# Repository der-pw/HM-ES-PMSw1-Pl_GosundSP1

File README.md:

# HM-ES-PMSw1-Pl_GosundSP1 PCB Version 2         

Umbau [Gosund SP1 bzw. BliTZWOLF SHP2](https://www.blitzwolf.com/Wifi-Smart-Socket-EU-p-244.html) zu HM-ES-PMSw1-Pl_SP1

In dieser Version 2 habe ich das Platinenlayout von [stan23](https://github.com/stan23) geändert.
Die SMD-Bauteile wurden auf Größe 0805 geändert und nur auf einer Seite arangiert, sodass einzig das Radio auf der Rückseite verbleibt und somit der Pinheader nicht mehr benötigt wird.

Weiterhin liegt das Original-Projekt hier: https://github.com/stan23/HM-ES-PMSw1-Pl_GosundSP1

Dies basiert auf der hervorragenden Arbeit von [pa-pa](https://github.com/pa-pa/AskSinPP) und [Jérôme](https://github.com/jp112sdl/Beispiel_AskSinPP).

*Achtung*: es kann verschiedene Versionen der Gosund/Blitzwolf-Stecker geben. Diese Platine passt bei folgender Version:

## Teileliste
Bauteil                  | Bestellnummer   | Anzahl | Kommentar
------------------------ | --------------- | ------ | ---------
C1                       | X5R-G0805 10/6  |   1    | -
C2 .. C6                 | X7R-G0805 100N  |   5    | -
R1                       | RND 0805 1 10K  |   1    | -
R2                       | RND 0805 1 1,0M |   1    | -
U1                       | ATMEGA 644PA-AU |   1    | -
Y1                       | CSTCE 8,00      |   1    | ist EOL, aber über Ali noch zu beziehen

## Vergleich:

## Eingebaut

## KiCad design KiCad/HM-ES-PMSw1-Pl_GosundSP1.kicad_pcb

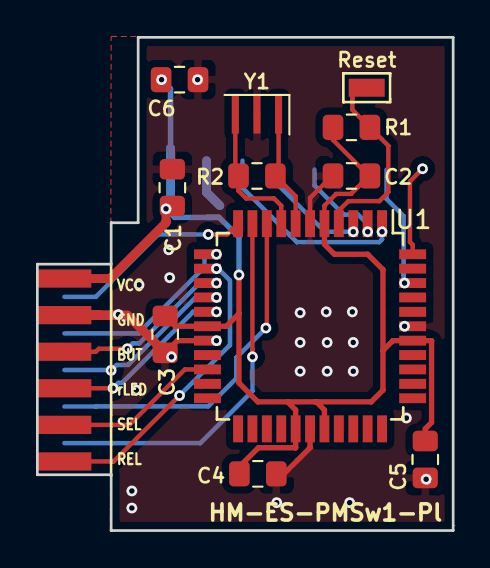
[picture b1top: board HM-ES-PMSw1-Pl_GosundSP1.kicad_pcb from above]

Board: 2 copper layers, 23.1 x 27.4 mm, 13 parts (1 on the bottom side), 19 nets.

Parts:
C1: 10u; C_0805_2012Metric_Pad1.15x1.40mm_HandSolder
C2, C3, C4, C5, C6: 100n; C_0805_2012Metric_Pad1.15x1.40mm_HandSolder
J4: Reset; Testpad
J11: BW_Gosund_Con; Gosund_SP1-C_V2.3
R1: 10k; R_0805_2012Metric_Pad1.15x1.40mm_HandSolder
R2: 1M; R_0805_2012Metric_Pad1.15x1.40mm_HandSolder
U1: ATMEGA644PA-AU; TQFP-44_10x10mm_Pitch0.8mm
U2: CC1101; CC1101_Module
Y1: Resonator; Resonator_SMD_muRata_TPSKA-3pin_7.9x3.8mm_HandSoldering

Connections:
/BUTTON: J11.BUT, U1.14
/CF: J11.CF, U1.12
/CF1: J11.CF1, U1.11
/CS: U1.44, U2.8
/GDO0: U1.42, U2.7
/LED_blue: J11.bLED, U1.15
/LED_red: J11.rLED, U1.16
/MISO: U1.2, U2.5
/MOSI: U1.1, U2.3
/RELAY: J11.REL, U1.13
/RESET: J4.1, R1.2, U1.4
/RX: J11.RX, U1.9
/SCK: U1.3, U2.4
/SEL: J11.SEL, U1.20
/TX: J11.TX, U1.10
GND: C1.2, C2.2, C3.2, C4.2, C5.2, C6.2, J11.GND, U1.6, U1.18, U1.28, U1.39, U2.2, U2.10, U2.11, Y1.2
unnamed: R2.1, U1.7, Y1.1
unnamed: R2.2, U1.8, Y1.3
VCC: C1.1, C2.1, C3.1, C4.1, C5.1, C6.1, J11.VCC, R1.1, U1.5, U1.17, U1.27, U1.29, U1.38, U2.1

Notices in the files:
KiCad/HM-ES-PMSw1-Pl_GosundSP1.kicad_pcb:
CC BY-NC-SA 4.0
README.md:
License: CC BY-NC-SA 4.0
